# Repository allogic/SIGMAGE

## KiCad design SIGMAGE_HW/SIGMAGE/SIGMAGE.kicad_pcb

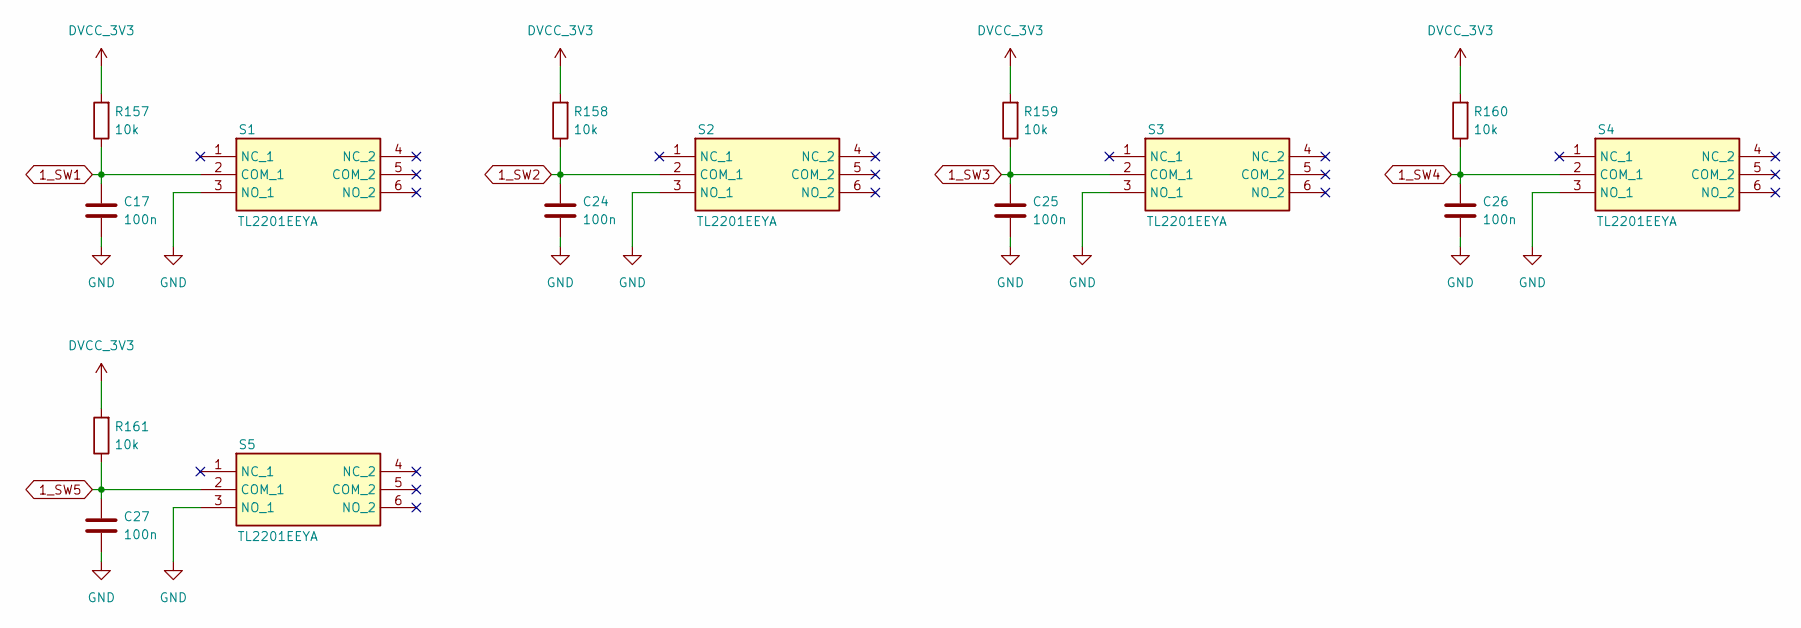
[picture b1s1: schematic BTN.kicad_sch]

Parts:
C17, C24, C25, C26, C27: 100n; C_0603_1608Metric
R157, R158, R159, R160, R161: 10k; R_0603_1608Metric
S1, S2, S3, S4, S5: TL2201EEYA; Manufacturer_Part_Number TL2201EEYA; Mouser Part Number 612-TL2201EEYA

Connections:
1_SW1: C17.1, R157.1, S1.2 (COM_1); also elsewhere on the board
1_SW2: C24.1, R158.1, S2.2 (COM_1); also elsewhere on the board
1_SW3: C25.1, R159.1, S3.2 (COM_1); also elsewhere on the board
1_SW4: C26.1, R160.1, S4.2 (COM_1); also elsewhere on the board
1_SW5: C27.1, R161.1, S5.2 (COM_1); also elsewhere on the board
DVCC_3V3: R157.2, R158.2, R159.2, R160.2, R161.2; also elsewhere on the board
GND: C17.2, C24.2, C25.2, C26.2, C27.2, S1.3 (NO_1), S2.3 (NO_1), S3.3 (NO_1), S4.3 (NO_1), S5.3 (NO_1); also elsewhere on the board

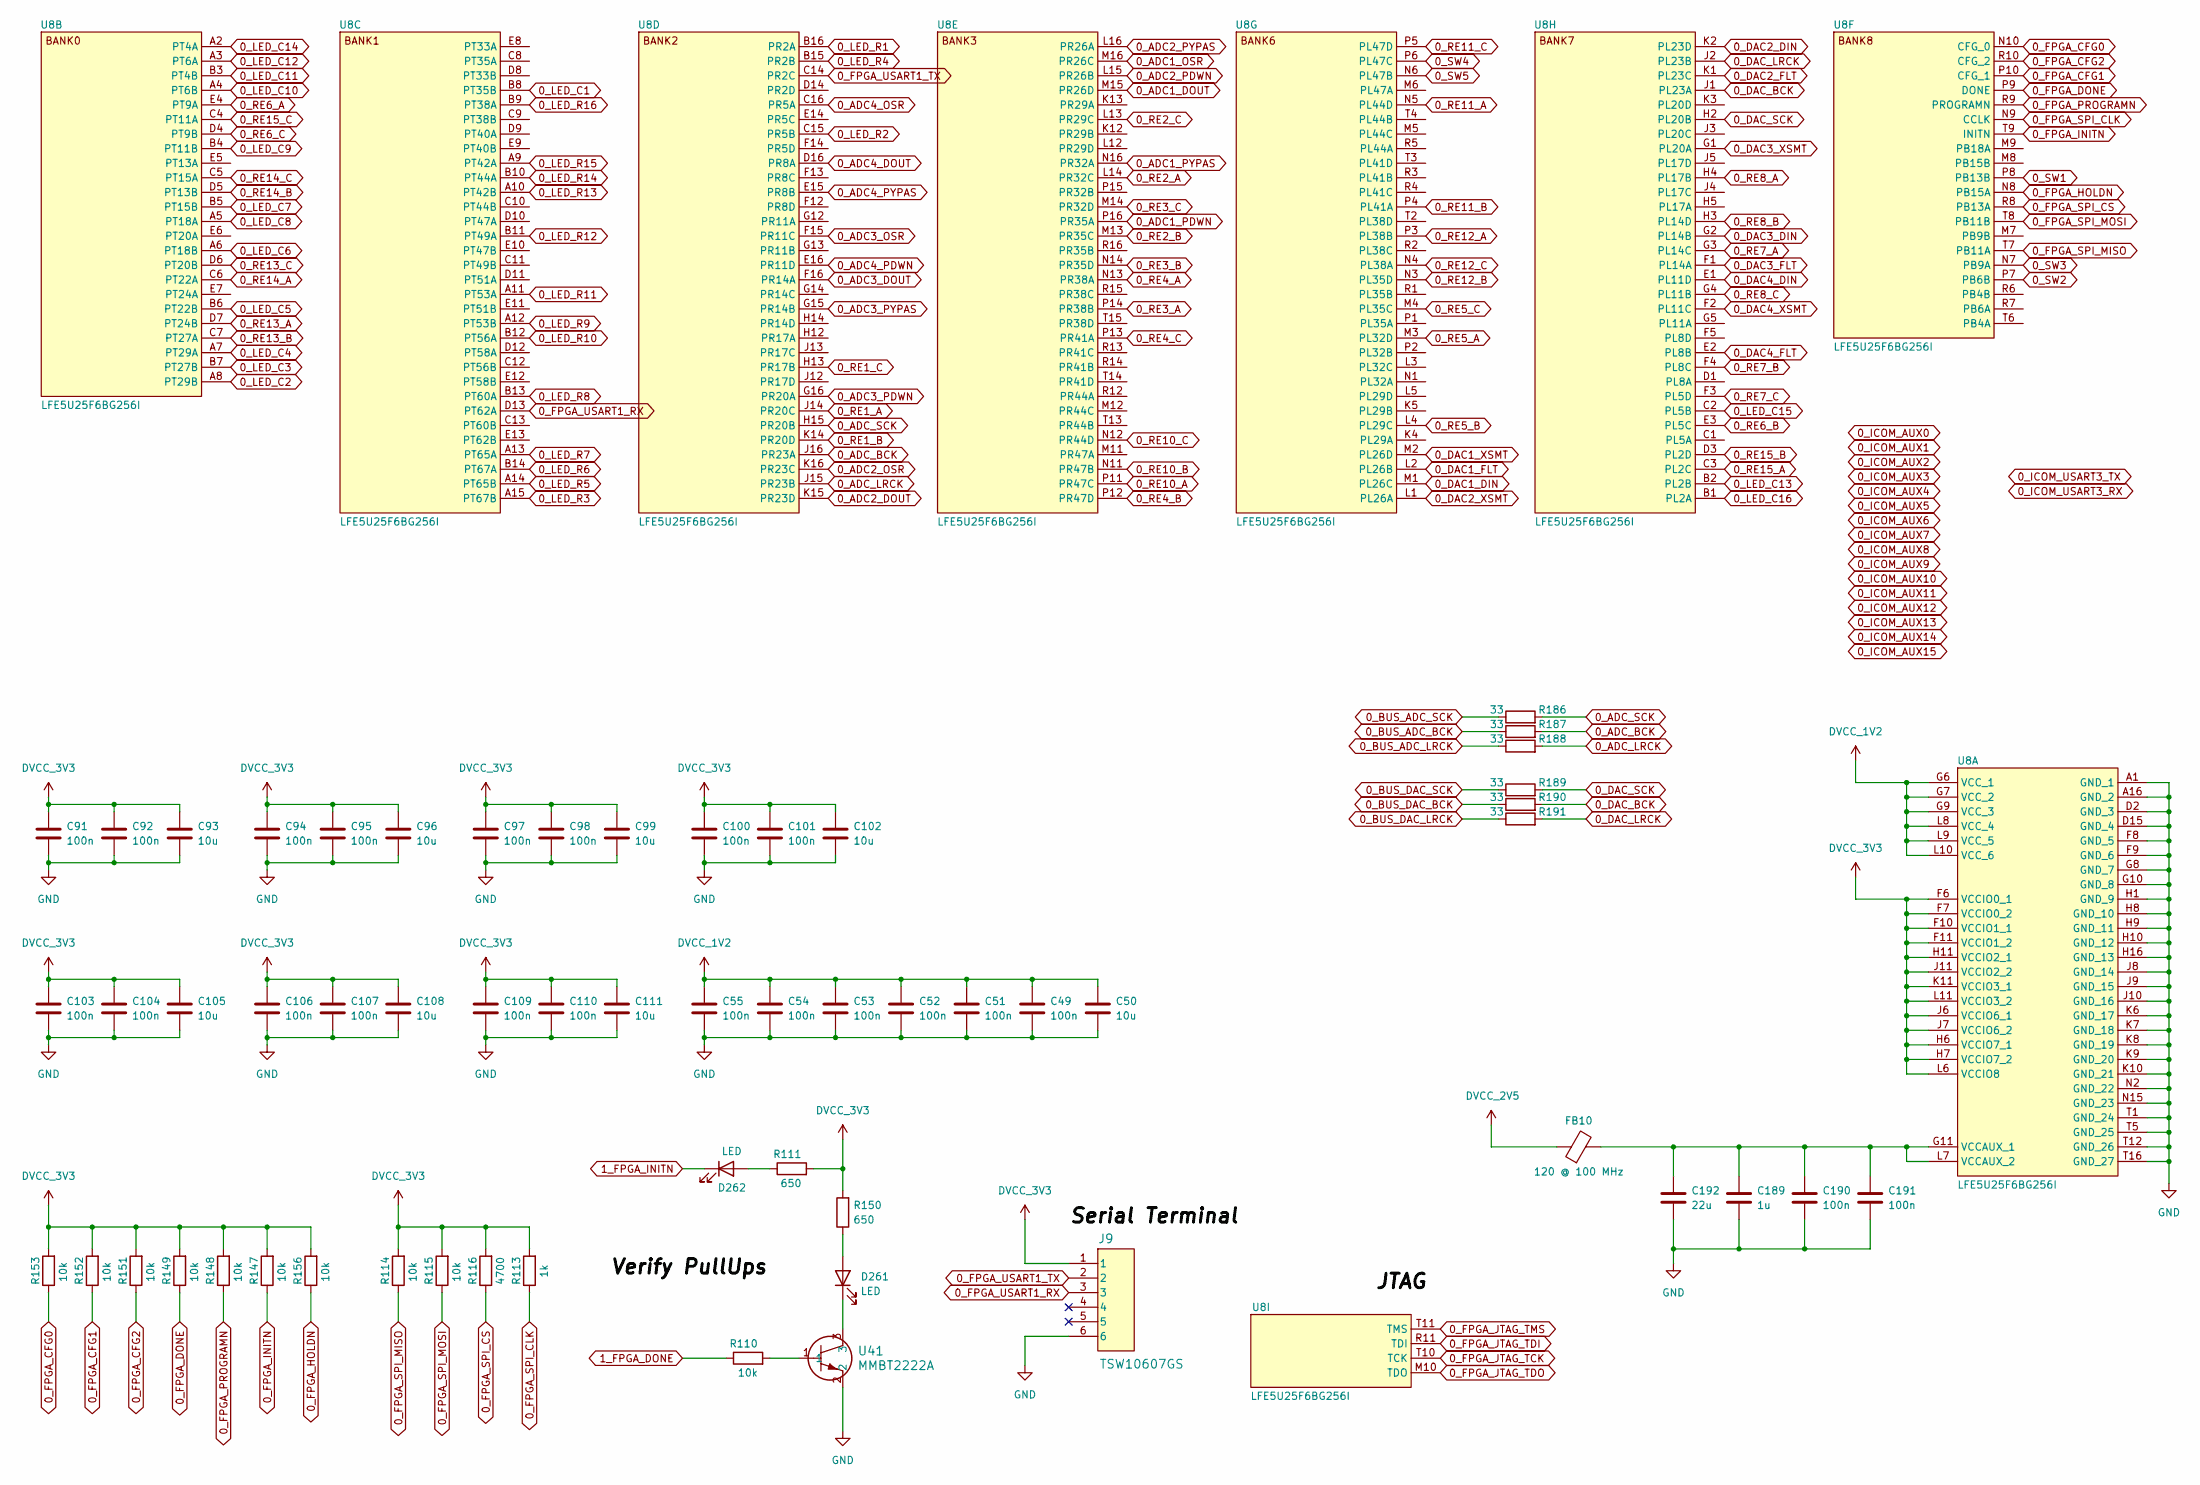
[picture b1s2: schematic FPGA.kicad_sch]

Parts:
C49, C51, C52, C53, C54, C55, C91, C92, C94, C95, C97, C98, C100, C101, C103, C104, C106, C107, C109, C110, C190, C191: 100n; C_0603_1608Metric
C50, C93, C96, C99, C102, C105, C108, C111: 10u; C_0603_1608Metric
C189: 1u; C_0603_1608Metric
C192: 22u; C_0603_1608Metric
D261, D262: LED; LED_0603_1608Metric
FB10: 120 @ 100 MHz; C_0603_1608Metric
J9: TSW10607GS
R110, R114, R115, R147, R148, R149, R151, R152, R153, R156: 10k; R_0603_1608Metric
R111, R150: 650; R_0603_1608Metric
R113: 1k; R_0603_1608Metric
R116: 4700; R_0603_1608Metric
R186, R187, R188, R189, R190, R191: 33; R_0603_1608Metric
U8: LFE5U25F6BG256I; Manufacturer_Part_Number LFE5U-25F-6BG256I; Mouser Part Number 842-LFE5U25F6BG256I
U41: MMBT2222A

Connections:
0_ADC1_DOUT: U8.M15 (PR26D); also elsewhere on the board
0_ADC1_OSR: U8.M16 (PR26C); also elsewhere on the board
0_ADC1_PDWN: U8.P16 (PR35A); also elsewhere on the board
0_ADC1_PYPAS: U8.N16 (PR32A); also elsewhere on the board
0_ADC2_DOUT: U8.K15 (PR23D); also elsewhere on the board
0_ADC2_OSR: U8.K16 (PR23C); also elsewhere on the board
0_ADC2_PDWN: U8.L15 (PR26B); also elsewhere on the board
0_ADC2_PYPAS: U8.L16 (PR26A); also elsewhere on the board
0_ADC3_DOUT: U8.F16 (PR14A); also elsewhere on the board
0_ADC3_OSR: U8.F15 (PR11C); also elsewhere on the board
0_ADC3_PDWN: U8.G16 (PR20A); also elsewhere on the board
0_ADC3_PYPAS: U8.G15 (PR14B); also elsewhere on the board
0_ADC4_DOUT: U8.D16 (PR8A); also elsewhere on the board
0_ADC4_OSR: U8.C16 (PR5A); also elsewhere on the board
0_ADC4_PDWN: U8.E16 (PR11D); also elsewhere on the board
0_ADC4_PYPAS: U8.E15 (PR8B); also elsewhere on the board
0_ADC_BCK: R187.2, U8.J16 (PR23A)
0_ADC_LRCK: R188.2, U8.J15 (PR23B)
0_ADC_SCK: R186.2, U8.H15 (PR20B)
0_BUS_ADC_BCK: R187.1; also elsewhere on the board
0_BUS_ADC_LRCK: R188.1; also elsewhere on the board
0_BUS_ADC_SCK: R186.1; also elsewhere on the board
0_BUS_DAC_BCK: R190.1; also elsewhere on the board
0_BUS_DAC_LRCK: R191.1; also elsewhere on the board
0_BUS_DAC_SCK: R189.1; also elsewhere on the board
0_DAC1_DIN: U8.M1 (PL26C); also elsewhere on the board
0_DAC1_FLT: U8.L2 (PL26B); also elsewhere on the board
0_DAC1_XSMT: U8.M2 (PL26D); also elsewhere on the board
0_DAC2_DIN: U8.K2 (PL23D); also elsewhere on the board
0_DAC2_FLT: U8.K1 (PL23C); also elsewhere on the board
0_DAC2_XSMT: U8.L1 (PL26A); also elsewhere on the board
0_DAC3_DIN: U8.G2 (PL14B); also elsewhere on the board
0_DAC3_FLT: U8.F1 (PL14A); also elsewhere on the board
0_DAC3_XSMT: U8.G1 (PL20A); also elsewhere on the board
0_DAC4_DIN: U8.E1 (PL11D); also elsewhere on the board
0_DAC4_FLT: U8.E2 (PL8B); also elsewhere on the board
0_DAC4_XSMT: U8.F2 (PL11C); also elsewhere on the board
0_DAC_BCK: R190.2, U8.J1 (PL23A)
0_DAC_LRCK: R191.2, U8.J2 (PL23B)
0_DAC_SCK: R189.2, U8.H2 (PL20B)
0_FPGA_CFG0: R153.1, U8.N10 (CFG_0); also elsewhere on the board
0_FPGA_CFG1: R152.1, U8.P10 (CFG_1); also elsewhere on the board
0_FPGA_CFG2: R151.1, U8.R10 (CFG_2); also elsewhere on the board
0_FPGA_DONE: R149.1, U8.P9 (DONE); also elsewhere on the board
0_FPGA_HOLDN: R156.1, U8.N8 (PB15A); also elsewhere on the board
0_FPGA_INITN: R147.1, U8.T9 (INITN); also elsewhere on the board
0_FPGA_JTAG_TCK: U8.T10 (TCK); also elsewhere on the board
0_FPGA_JTAG_TDI: U8.R11 (TDI); also elsewhere on the board
0_FPGA_JTAG_TDO: U8.M10 (TDO); also elsewhere on the board
0_FPGA_JTAG_TMS: U8.T11 (TMS); also elsewhere on the board
0_FPGA_PROGRAMN: R148.1, U8.R9 (PROGRAMN); also elsewhere on the board
0_FPGA_SPI_CLK: R113.1, U8.N9 (CCLK); also elsewhere on the board
0_FPGA_SPI_CS: R116.1, U8.R8 (PB13A); also elsewhere on the board
0_FPGA_SPI_MISO: R114.1, U8.T7 (PB11A); also elsewhere on the board
0_FPGA_SPI_MOSI: R115.1, U8.T8 (PB11B); also elsewhere on the board
0_FPGA_USART1_RX: J9.3, U8.D13 (PT62A)
0_FPGA_USART1_TX: J9.2, U8.C14 (PR2C)
0_LED_C1: U8.B8 (PT35B); also elsewhere on the board
0_LED_C2: U8.A8 (PT29B); also elsewhere on the board
0_LED_C3: U8.B7 (PT27B); also elsewhere on the board
0_LED_C4: U8.A7 (PT29A); also elsewhere on the board
0_LED_C5: U8.B6 (PT22B); also elsewhere on the board
0_LED_C6: U8.A6 (PT18B); also elsewhere on the board
0_LED_C7: U8.B5 (PT15B); also elsewhere on the board
0_LED_C8: U8.A5 (PT18A); also elsewhere on the board
0_LED_C9: U8.B4 (PT11B); also elsewhere on the board
0_LED_C10: U8.A4 (PT6B); also elsewhere on the board
0_LED_C11: U8.B3 (PT4B); also elsewhere on the board
0_LED_C12: U8.A3 (PT6A); also elsewhere on the board
0_LED_C13: U8.B2 (PL2B); also elsewhere on the board
0_LED_C14: U8.A2 (PT4A); also elsewhere on the board
0_LED_C15: U8.C2 (PL5B); also elsewhere on the board
0_LED_C16: U8.B1 (PL2A); also elsewhere on the board
0_LED_R1: U8.B16 (PR2A); also elsewhere on the board
0_LED_R2: U8.C15 (PR5B); also elsewhere on the board
0_LED_R3: U8.A15 (PT67B); also elsewhere on the board
0_LED_R4: U8.B15 (PR2B); also elsewhere on the board
0_LED_R5: U8.A14 (PT65B); also elsewhere on the board
0_LED_R6: U8.B14 (PT67A); also elsewhere on the board
0_LED_R7: U8.A13 (PT65A); also elsewhere on the board
0_LED_R8: U8.B13 (PT60A); also elsewhere on the board
0_LED_R9: U8.A12 (PT53B); also elsewhere on the board
0_LED_R10: U8.B12 (PT56A); also elsewhere on the board
0_LED_R11: U8.A11 (PT53A); also elsewhere on the board
0_LED_R12: U8.B11 (PT49A); also elsewhere on the board
0_LED_R13: U8.A10 (PT42B); also elsewhere on the board
0_LED_R14: U8.B10 (PT44A); also elsewhere on the board
0_LED_R15: U8.A9 (PT42A); also elsewhere on the board
0_LED_R16: U8.B9 (PT38A); also elsewhere on the board
0_RE1_A: U8.J14 (PR20C); also elsewhere on the board
0_RE1_B: U8.K14 (PR20D); also elsewhere on the board
0_RE1_C: U8.H13 (PR17B); also elsewhere on the board
0_RE2_A: U8.L14 (PR32C); also elsewhere on the board
0_RE2_B: U8.M13 (PR35C); also elsewhere on the board
0_RE2_C: U8.L13 (PR29C); also elsewhere on the board
0_RE3_A: U8.P14 (PR38B); also elsewhere on the board
0_RE3_B: U8.N14 (PR35D); also elsewhere on the board
0_RE3_C: U8.M14 (PR32D); also elsewhere on the board
0_RE4_A: U8.N13 (PR38A); also elsewhere on the board
0_RE4_B: U8.P12 (PR47D); also elsewhere on the board
0_RE4_C: U8.P13 (PR41A); also elsewhere on the board
0_RE5_A: U8.M3 (PL32D); also elsewhere on the board
0_RE5_B: U8.L4 (PL29C); also elsewhere on the board
0_RE5_C: U8.M4 (PL35C); also elsewhere on the board
0_RE6_A: U8.E4 (PT9A); also elsewhere on the board
0_RE6_B: U8.E3 (PL5C); also elsewhere on the board
0_RE6_C: U8.D4 (PT9B); also elsewhere on the board
0_RE7_A: U8.G3 (PL14C); also elsewhere on the board
0_RE7_B: U8.F4 (PL8C); also elsewhere on the board
0_RE7_C: U8.F3 (PL5D); also elsewhere on the board
0_RE8_A: U8.H4 (PL17B); also elsewhere on the board
0_RE8_B: U8.H3 (PL14D); also elsewhere on the board
0_RE8_C: U8.G4 (PL11B); also elsewhere on the board
0_RE10_A: U8.P11 (PR47C); also elsewhere on the board
0_RE10_B: U8.N11 (PR47B); also elsewhere on the board
0_RE10_C: U8.N12 (PR44D); also elsewhere on the board
0_RE11_A: U8.N5 (PL44D); also elsewhere on the board
0_RE11_B: U8.P4 (PL41A); also elsewhere on the board
0_RE11_C: U8.P5 (PL47D); also elsewhere on the board
0_RE12_A: U8.P3 (PL38B); also elsewhere on the board
0_RE12_B: U8.N3 (PL35D); also elsewhere on the board
0_RE12_C: U8.N4 (PL38A); also elsewhere on the board
0_RE13_A: U8.D7 (PT24B); also elsewhere on the board
0_RE13_B: U8.C7 (PT27A); also elsewhere on the board
0_RE13_C: U8.D6 (PT20B); also elsewhere on the board
0_RE14_A: U8.C6 (PT22A); also elsewhere on the board
0_RE14_B: U8.D5 (PT13B); also elsewhere on the board
0_RE14_C: U8.C5 (PT15A); also elsewhere on the board
0_RE15_A: U8.C3 (PL2C); also elsewhere on the board
0_RE15_B: U8.D3 (PL2D); also elsewhere on the board
0_RE15_C: U8.C4 (PT11A); also elsewhere on the board
0_SW1: U8.P8 (PB13B); also elsewhere on the board
0_SW2: U8.P7 (PB6B); also elsewhere on the board
0_SW3: U8.N7 (PB9A); also elsewhere on the board
0_SW4: U8.P6 (PL47C); also elsewhere on the board
0_SW5: U8.N6 (PL47B); also elsewhere on the board
1_FPGA_DONE: R110.1; also elsewhere on the board
1_FPGA_INITN: D262.1 (K); also elsewhere on the board
DVCC_1V2: C49.1, C50.1, C51.1, C52.1, C53.1, C54.1, C55.1, U8.G6 (VCC_1), U8.G7 (VCC_2), U8.G9 (VCC_3), U8.L8 (VCC_4), U8.L9 (VCC_5), U8.L10 (VCC_6); also elsewhere on the board
DVCC_2V5: FB10.1; also elsewhere on the board
DVCC_3V3: C91.1, C92.1, C93.1, C94.1, C95.1, C96.1, C97.1, C98.1, C99.1, C100.1, C101.1, C102.1, C103.1, C104.1, C105.1, C106.1, C107.1, C108.1, C109.1, C110.1, C111.1, J9.1, R111.2, R113.2, R114.2, R115.2, R116.2, R147.2, R148.2, R149.2, R150.2, R151.2, R152.2, R153.2, R156.2, U8.F6 (VCCIO0_1), U8.F7 (VCCIO0_2), U8.F10 (VCCIO1_1), U8.F11 (VCCIO1_2), U8.H6 (VCCIO7_1), U8.H7 (VCCIO7_2), U8.H11 (VCCIO2_1), U8.J6 (VCCIO6_1), U8.J7 (VCCIO6_2), U8.J11 (VCCIO2_2), U8.K11 (VCCIO3_1), U8.L6 (VCCIO8), U8.L11 (VCCIO3_2); also elsewhere on the board
GND: C49.2, C50.2, C51.2, C52.2, C53.2, C54.2, C55.2, C91.2, C92.2, C93.2, C94.2, C95.2, C96.2, C97.2, C98.2, C99.2, C100.2, C101.2, C102.2, C103.2, C104.2, C105.2, C106.2, C107.2, C108.2, C109.2, C110.2, C111.2, C189.2, C190.2, C191.2, C192.2, J9.6, U8.A1 (GND_1), U8.A16 (GND_2), U8.D2 (GND_3), U8.D15 (GND_4), U8.F8 (GND_5), U8.F9 (GND_6), U8.G8 (GND_7), U8.G10 (GND_8), U8.H1 (GND_9), U8.H8 (GND_10), U8.H9 (GND_11), U8.H10 (GND_12), U8.H16 (GND_13), U8.J8 (GND_14), U8.J9 (GND_15), U8.J10 (GND_16), U8.K6 (GND_17), U8.K7 (GND_18), U8.K8 (GND_19), U8.K9 (GND_20), U8.K10 (GND_21), U8.N2 (GND_22), U8.N15 (GND_23), U8.T1 (GND_24), U8.T5 (GND_25), U8.T12 (GND_26), U8.T16 (GND_27), U41.2; also elsewhere on the board
unnamed: D261.2 (A), R150.1
unnamed: D261.1 (K), U41.3
unnamed: D262.2 (A), R111.1
unnamed: R110.2, U41.1
unnamed: C189.1, C190.1, C191.1, C192.1, FB10.2, U8.G11 (VCCAUX_1), U8.L7 (VCCAUX_2)

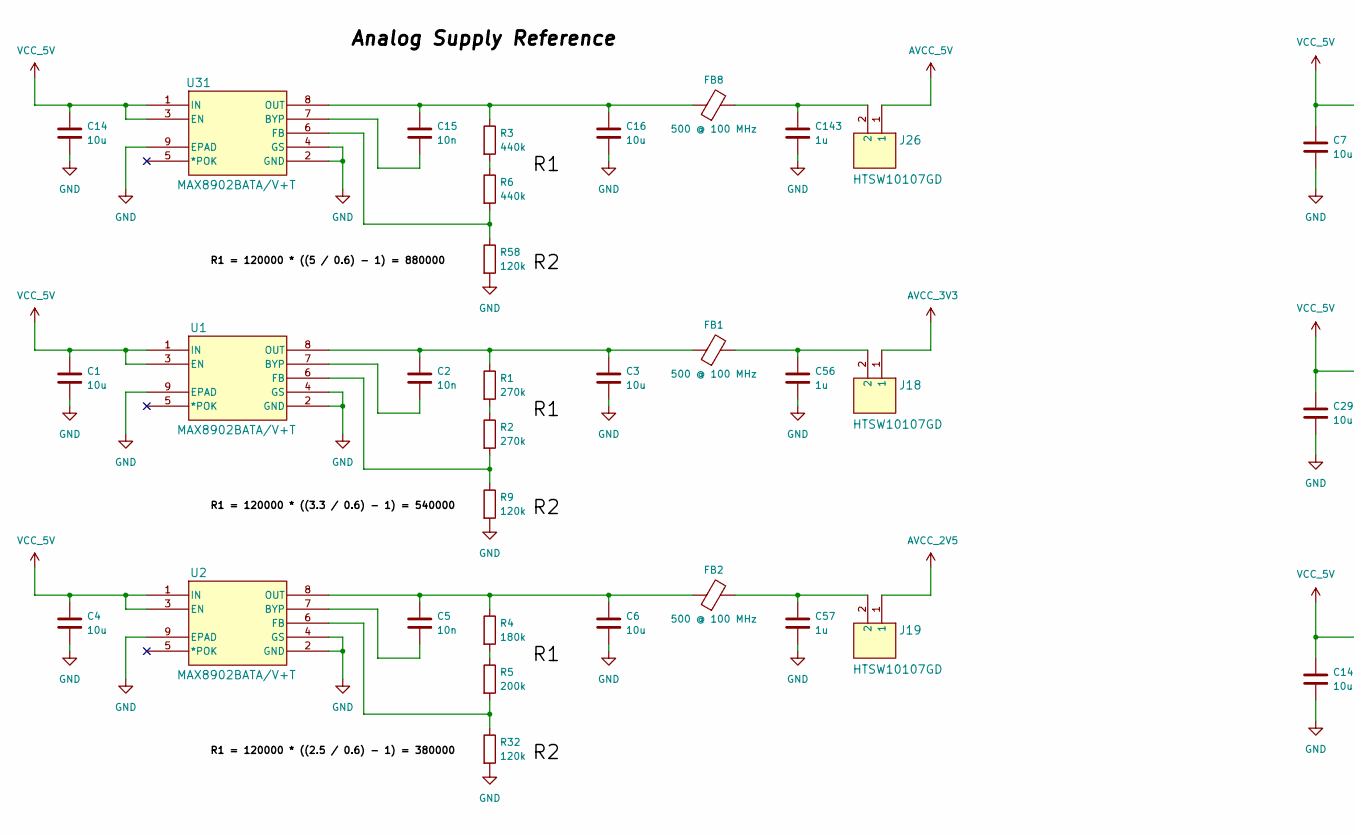
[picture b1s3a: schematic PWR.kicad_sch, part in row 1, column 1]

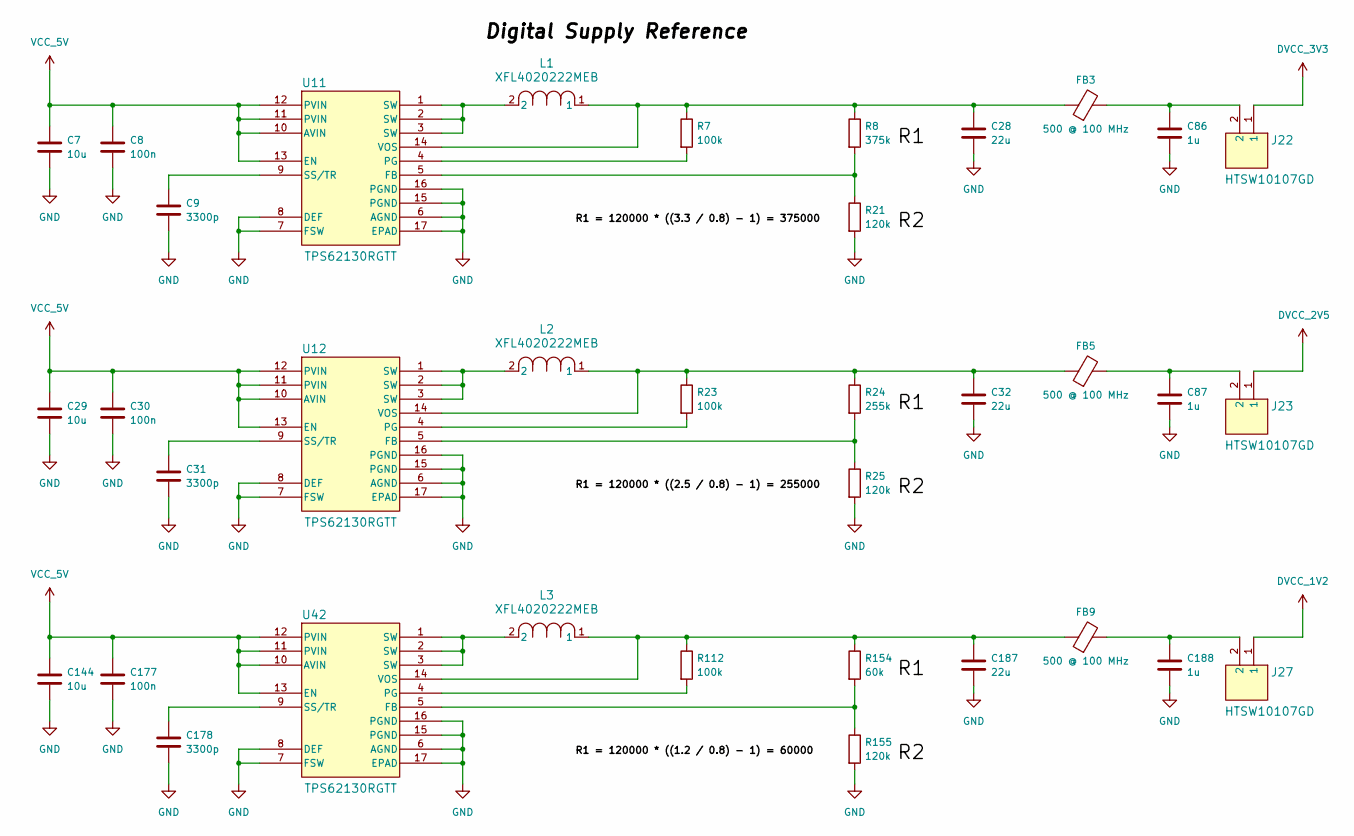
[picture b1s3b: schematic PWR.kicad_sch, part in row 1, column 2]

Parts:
C1, C3, C4, C6, C7, C14, C16, C29, C144: 10u; C_0603_1608Metric
C2, C5, C15: 10n; C_0603_1608Metric
C8, C30, C177: 100n; C_0603_1608Metric
C9, C31, C178: 3300p; C_0603_1608Metric
C28, C32, C187: 22u; C_0603_1608Metric
C56, C57, C86, C87, C143, C188: 1u; C_0603_1608Metric
FB1, FB2, FB3, FB5, FB8, FB9: 500 @ 100 MHz; C_0603_1608Metric
J18, J19, J22, J23, J26, J27: HTSW10107GD
L1, L2, L3: XFL4020222MEB
R1, R2: 270k; R_0603_1608Metric
R3, R6: 440k; R_0603_1608Metric
R4: 180k; R_0603_1608Metric
R5: 200k; R_0603_1608Metric
R7, R23, R112: 100k; R_0603_1608Metric
R8: 375k; R_0603_1608Metric
R9, R21, R25, R32, R58, R155: 120k; R_0603_1608Metric
R24: 255k; R_0603_1608Metric
R154: 60k; R_0603_1608Metric
U1, U2, U31: MAX8902BATA/V+T; MAX8902BATAVT
U11, U12, U42: TPS62130RGTT

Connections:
AVCC_2V5: J19.1; also elsewhere on the board
AVCC_3V3: J18.1; also elsewhere on the board
AVCC_5V: J26.1; also elsewhere on the board
DVCC_1V2: J27.1; also elsewhere on the board
DVCC_2V5: J23.1; also elsewhere on the board
DVCC_3V3: J22.1; also elsewhere on the board
GND: C1.2, C3.2, C4.2, C6.2, C7.2, C8.2, C9.2, C14.2, C16.2, C28.2, C29.2, C30.2, C31.2, C32.2, C56.2, C57.2, C86.2, C87.2, C143.2, C144.2, C177.2, C178.2, C187.2, C188.2, R9.2, R21.2, R25.2, R32.2, R58.2, R155.2, U1.2 (GND), U1.4 (GS), U1.9 (EPAD), U2.2 (GND), U2.4 (GS), U2.9 (EPAD), U11.6 (AGND), U11.7 (FSW), U11.8 (DEF), U11.15 (PGND), U11.16 (PGND), U11.17 (EPAD), U12.6 (AGND), U12.7 (FSW), U12.8 (DEF), U12.15 (PGND), U12.16 (PGND), U12.17 (EPAD), U31.2 (GND), U31.4 (GS), U31.9 (EPAD), U42.6 (AGND), U42.7 (FSW), U42.8 (DEF), U42.15 (PGND), U42.16 (PGND), U42.17 (EPAD); also elsewhere on the board
unnamed: C56.1, FB1.2, J18.2
unnamed: C57.1, FB2.2, J19.2
unnamed: C86.1, FB3.2, J22.2
unnamed: C87.1, FB5.2, J23.2
unnamed: C143.1, FB8.2, J26.2
unnamed: C188.1, FB9.2, J27.2
unnamed: L1.2, U11.1 (SW), U11.2 (SW), U11.3 (SW)
unnamed: L2.2, U12.1 (SW), U12.2 (SW), U12.3 (SW)
unnamed: L3.2, U42.1 (SW), U42.2 (SW), U42.3 (SW)
unnamed: R1.2, R2.1
unnamed: R3.2, R6.1
unnamed: R4.2, R5.1
unnamed: C2.2, U1.7 (BYP)
unnamed: R2.2, R9.1, U1.6 (FB)
unnamed: C2.1, C3.1, FB1.1, R1.1, U1.8 (OUT)
unnamed: C5.2, U2.7 (BYP)
unnamed: R5.2, R32.1, U2.6 (FB)
unnamed: C5.1, C6.1, FB2.1, R4.1, U2.8 (OUT)
unnamed: R8.2, R21.1, U11.5 (FB)
unnamed: R7.2, U11.4 (PG)
unnamed: C9.1, U11.9 (SS/TR)
unnamed: C28.1, FB3.1, L1.1, R7.1, R8.1, U11.14 (VOS)
unnamed: R24.2, R25.1, U12.5 (FB)
unnamed: R23.2, U12.4 (PG)
unnamed: C31.1, U12.9 (SS/TR)
unnamed: C32.1, FB5.1, L2.1, R23.1, R24.1, U12.14 (VOS)
unnamed: C15.2, U31.7 (BYP)
unnamed: R6.2, R58.1, U31.6 (FB)
unnamed: C15.1, C16.1, FB8.1, R3.1, U31.8 (OUT)
unnamed: R154.2, R155.1, U42.5 (FB)
unnamed: R112.2, U42.4 (PG)
unnamed: C178.1, U42.9 (SS/TR)
unnamed: C187.1, FB9.1, L3.1, R112.1, R154.1, U42.14 (VOS)
